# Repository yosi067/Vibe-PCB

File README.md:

# 🔧 Vibe-PCB Orchestrator

**Hardware Design as Code — Compile, Check, Fabricate**

用 Python 寫電路、自動產生 PCB、靜態分析、3D 互動預覽——從程式碼到實體電路板的一條龍自動化框架。

> 🌐 **[線上 Demo (GitHub Pages)](https://yosi067.github.io/Vibe-PCB/)** — 即時預覽 PCB 2D 佈局、電路原理圖、3D 互動模型

---

## 目錄

- [專案架構](#專案架構)
- [自動化管線](#自動化管線)
- [模組總覽](#模組總覽)
- [核心功能](#核心功能)
- [快速開始](#快速開始)
- [詳細規格文件](#詳細規格文件)
- [擴展新電路](#擴展新電路)
- [License](#license)

---

## 專案架構

```
Vibe-PCB/
├── main.py                      # 主調度程式 — 雙模組管線
├── circuits/
│   ├── fan_controller.py        # 🌀 模組一：EMC2103 風扇控制器
│   └── power_monitor.py         # ⚡ 模組二：INA226 功耗監測
├── lib/
│   ├── analyzer.py              # 靜態分析引擎 (電壓守衛 + BOM + P=I²R + I2C 衝突)
│   ├── pcb_generator.py         # 風扇控制器 PCB 佈局產生器
│   ├── pcb_generator_power.py   # 功耗監測 PCB 佈局產生器
│   ├── sch_generator.py         # 風扇控制器原理圖產生器
│   ├── sch_generator_power.py   # 功耗監測原理圖產生器
│   ├── exporter.py              # KiCad CLI / Gerber / STEP 匯出
│   └── web_server.py            # 本地預覽伺服器
├── docs/
│   ├── module-fan-controller.md # 🌀 風扇控制器詳細規格（中文）
│   └── module-power-monitor.md  # ⚡ 功耗監測詳細規格（中文）
├── output/                      # 自動產出
│   ├── index.html               # 互動式預覽頁面 (KiCanvas + Three.js)
│   ├── fan_controller.kicad_pcb # 風扇控制器 PCB
│   ├── fan_controller.kicad_sch # 風扇控制器原理圖
│   ├── fan_controller.net       # 風扇控制器 Netlist
│   ├── power_monitor.kicad_pcb  # 功耗監測 PCB
│   ├── power_monitor.kicad_sch  # 功耗監測原理圖
│   └── power_monitor.net        # 功耗監測 Netlist
└── .github/workflows/deploy.yml # GitHub Pages 自動部署
```

---

## 自動化管線

```
  Step 1            Step 2           Step 3            Step 4            Step 5
[SKiDL Code] → [Netlist .net] → [Static Analysis] → [PCB + SCH] → [Web Preview]
  Python 電路       編譯產出        電壓/BOM/功耗       佈局 & 原理圖     KiCanvas +
  定義               SKiDL          P=I²R / I2C         自動生成         Three.js 3D
                                    衝突偵測
```

兩個模組 **同時平行** 執行整條管線，最終合併到同一個預覽頁面。

---

## 模組總覽

### 🌀 模組一：AI Server 風扇控制器

| 項目 | 規格 |
|------|------|
| 核心晶片 | Microchip EMC2103 (QFN-20, 4×4mm) |
| I2C 地址 | 0x2E (ADDR_SEL=GND) |
| 電壓域 | 3.3V (邏輯) + 12V (風扇供電) |
| PCB 尺寸 | 40mm × 30mm, 2 層 |
| 主要功能 | PWM 風扇轉速控制、Tach 轉速回饋、SMBALERT# 過溫通知 |
| BOM 成本 | ≈ $3.22 |

### ⚡ 模組二：Smart Power Monitor

| 項目 | 規格 |
|------|------|
| 核心晶片 | Texas Instruments INA226 (MSOP-10, 3×3mm) |
| I2C 地址 | 0x41 (A0=VCC, A1=GND) |
| 分流電阻 | 0.002Ω (2mΩ), 2512 封裝, 額定 2W |
| 設計電流 | 最大 30A (P=1.8W < 2W ✔) |
| PCB 尺寸 | 35mm × 25mm, 2 層 |
| 主要功能 | 12V 電壓/電流/功率即時監測、ALERT 過流告警 + LED |
| BOM 成本 | ≈ $5.22 |

---

## 核心功能

### ⚡ Voltage Guard — 電壓守衛
掃描 Netlist 中每個腳位的電壓域，自動偵測：
- 12V 訊號直連 3.3V IC → **ERROR**
- 跨電壓域零件缺少 Level Shift → **WARNING**

### 🔥 P=I²R 功耗檢查
自動計算每個電阻在最大電流下的功耗，比對封裝額定瓦數：
- Rs1 (0.002Ω, 2512): 1.8W < 2W → **PASS**
- 如果有人用 0402 封裝放 2mΩ → **FAIL** (超過 0.0625W)

### 🔗 I2C 位址衝突偵測
掃描所有模組的 I2C 設備，確認：
- Fan Controller: 0x2E ✔
- Power Monitor: 0x41 ✔
- 無衝突 → **PASS**

### 📦 BOM — 零件合規 & 成本估算
- 自動驗證封裝是否在已知庫中
- 根據零件類型估算 BOM 成本

### 🌐 互動式 Web 預覽
- **KiCanvas** 渲染 PCB 2D 佈局 + 電路原理圖（支援方向鍵平移、滾輪縮放）
- **Three.js** 3D 互動模型：
  - 🌀 風扇旋轉動畫 (PWM 控制轉速)
  - 🔵🟢🟠 訊號流粒子 (I2C / PWM / 12V)
  - 🔴 熱效應光暈 (Thermal 模擬)
  - 📊 即時數據顯示
- **模組切換器**：一鍵切換查看兩個模組的所有內容

---

## 快速開始

### 1. 環境準備

```bash
# Python 3.10+
pip install skidl
```

> **不需要安裝 KiCad！** 所有 .kicad_pcb / .kicad_sch 檔案由 Python 純文字產生。

### 2. 執行完整管線

```bash
python main.py
```

這會依序執行：編譯兩個電路 → 靜態分析 → 產生 PCB & 原理圖 → 啟動本地預覽伺服器

### 3. 常用選項

```bash
python main.py --analyze-only   # 僅編譯 + 靜態檢查，不啟動伺服器
python main.py --strict          # 嚴格模式（任何錯誤即中止）
python main.py --no-preview      # 跳過 Web 預覽伺服器
```

### 4. 線上預覽

無需本地執行，直接訪問 GitHub Pages：

👉 **https://yosi067.github.io/Vibe-PCB/**

---

## 詳細規格文件

> 為初學者撰寫的中文技術文件，涵蓋每個零件的選型理由、電路原理、PCB 設計要點。  
> 搭配線上 Demo 逐一對照，幫助你從零開始理解 PCB 設計。

| 文件 | 說明 |
|------|------|
| [🌀 風扇控制器詳細規格](docs/module-fan-controller.md) | EMC2103 電路結構、QFN-20 封裝、I2C 通訊、PWM 控制、去耦電容設計、3D 模型說明 |
| [⚡ 功耗監測詳細規格](docs/module-power-monitor.md) | INA226 電流量測原理 ($V=IR$)、分流電阻 P=I²R 選型計算、Kelvin 連接、Alert LED、大電流 PCB 走線 |

---

## 擴展新電路

在 `circuits/` 下新增 `.py` 檔案，參考現有模組的模式：

```python
# circuits/your_module.py
from skidl import Part, Pin, Net, POWER, TEMPLATE, SKIDL, generate_netlist, reset

def gen_your_module():
    reset()
    # 定義零件模板、網路、連接...
    generate_netlist(file_="output/your_module.net")
    return {"nets": {...}, "parts": {...}}
```

然後在 `main.py` 中加入新模組的編譯、分析、匯出步驟即可。

---

## License

MIT

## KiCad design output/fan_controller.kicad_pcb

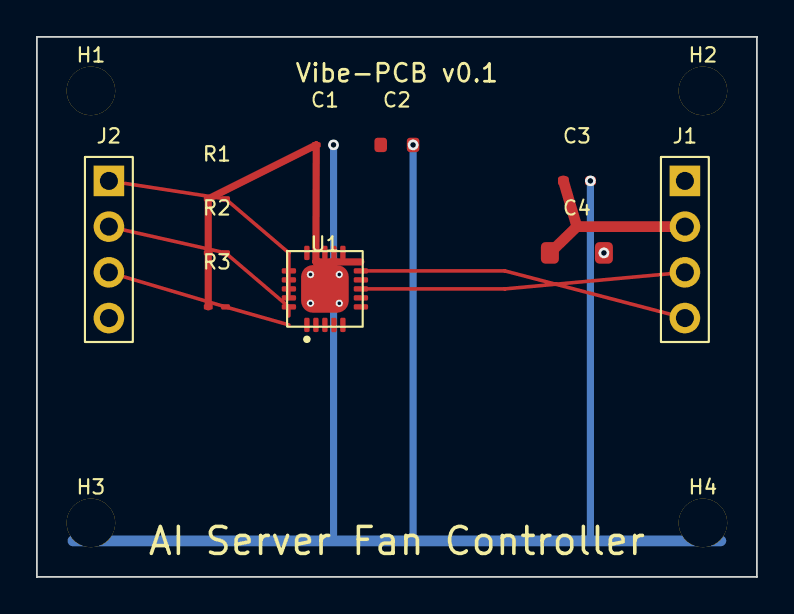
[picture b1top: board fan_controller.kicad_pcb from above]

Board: 2 copper layers, 40.0 x 30.0 mm, 14 parts (0 on the bottom side), 8 nets.

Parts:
C1: 100nF; C_0402_1005Metric
C2: 10uF; C_0805_2012Metric
C3: 100nF; C_0603_1608Metric
C4: 100uF; C_1206_3216Metric
H1, H2, H3, H4: MH; MountingHole_2.7mm_M2.5
J1: FAN_4PIN; PinHeader_1x04_P2.54mm_Vertical
J2: BMC_I2C; PinHeader_1x04_P2.54mm_Vertical
R1, R2: 4.7k; R_0402_1005Metric
R3: 10k; R_0402_1005Metric
U1: EMC2103; QFN-20-1EP_4x4mm_P0.5mm_EP2.65x2.65mm

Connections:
3V3: C1.1, C2.1, R1.1, R2.1, R3.1, U1.7, U1.8
12V: C3.1, C4.1, J1.2
FAN_PWM: J1.4, U1.2
FAN_TACH: J1.3, U1.1
GND: C1.2, C2.2, C3.2, C4.2, J1.1, J2.4, U1.6, U1.9, U1.21
I2C_SCL: J2.2, R2.2, U1.5
I2C_SDA: J2.1, R1.2, U1.4
SMBALERT_N: J2.3, R3.2, U1.3

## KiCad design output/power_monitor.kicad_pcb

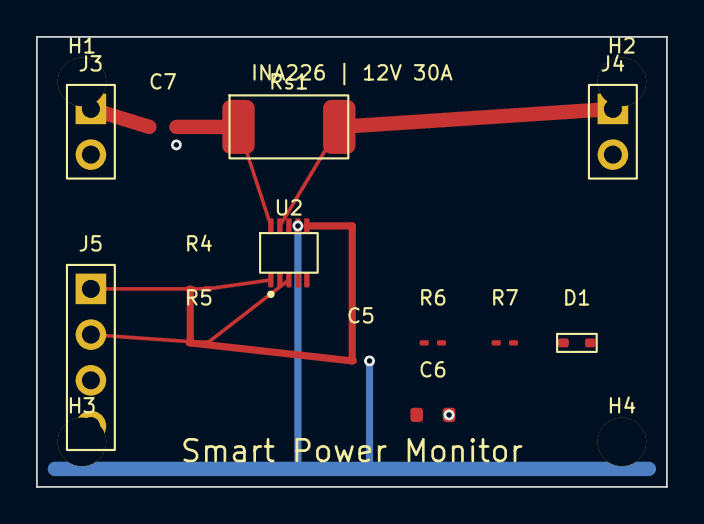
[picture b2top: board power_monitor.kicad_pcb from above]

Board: 2 copper layers, 35.0 x 25.0 mm, 17 parts (0 on the bottom side), 7 nets.

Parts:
C5: 100nF; C_0402_1005Metric
C6: 10uF; C_0805_2012Metric
C7: 100nF; C_0603_1608Metric
D1: RED; LED_0603_1608Metric
H1, H2, H3, H4: MH; MountingHole_2.7mm_M2.5
J3: 12V_IN; PinHeader_1x02_P2.54mm_Vertical
J4: 12V_OUT; PinHeader_1x02_P2.54mm_Vertical
J5: BMC_PWR; PinHeader_1x04_P2.54mm_Vertical
R4, R5: 4.7k; R_0402_1005Metric
R6: 10k; R_0402_1005Metric
R7: 1k; R_0402_1005Metric
Rs1: 2mΩ; R_2512_6332Metric
U2: INA226; MSOP-10_3x3mm_P0.5mm

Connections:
3V3: C5.1, C6.1, R4.1, R5.1, R6.1, U2.2, U2.6
12V_INPUT: C7.1, J3.1, Rs1.1, U2.10
12V_OUTPUT: J4.1, Rs1.2, U2.8, U2.9
GND: C5.2, C6.2, C7.2, D1.1, D1.2, J3.2, J4.2, J5.4, R7.2, U2.1, U2.7
I2C_SCL: J5.2, R5.2, U2.5
I2C_SDA: J5.1, R4.2, U2.4
PWR_ALERT_N: J5.3, R6.2, R7.1, U2.3

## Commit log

2026-04-18 feat: multi-module PCB system + GitHub Pages CI/CD
    - Fan Controller (EMC2103) + Power Monitor (INA226)
    - KiCanvas 2D PCB/Schematic viewer with module switcher
    - Three.js 3D model with dynamic animations
    - P=I²R power check, I2C conflict detection, BOM cost estimation
    - GitHub Actions workflow for auto-deploy to Pages
2026-04-18 docs: 更新 README + 新增中文模組規格文件 (fan-controller, power-monitor)
